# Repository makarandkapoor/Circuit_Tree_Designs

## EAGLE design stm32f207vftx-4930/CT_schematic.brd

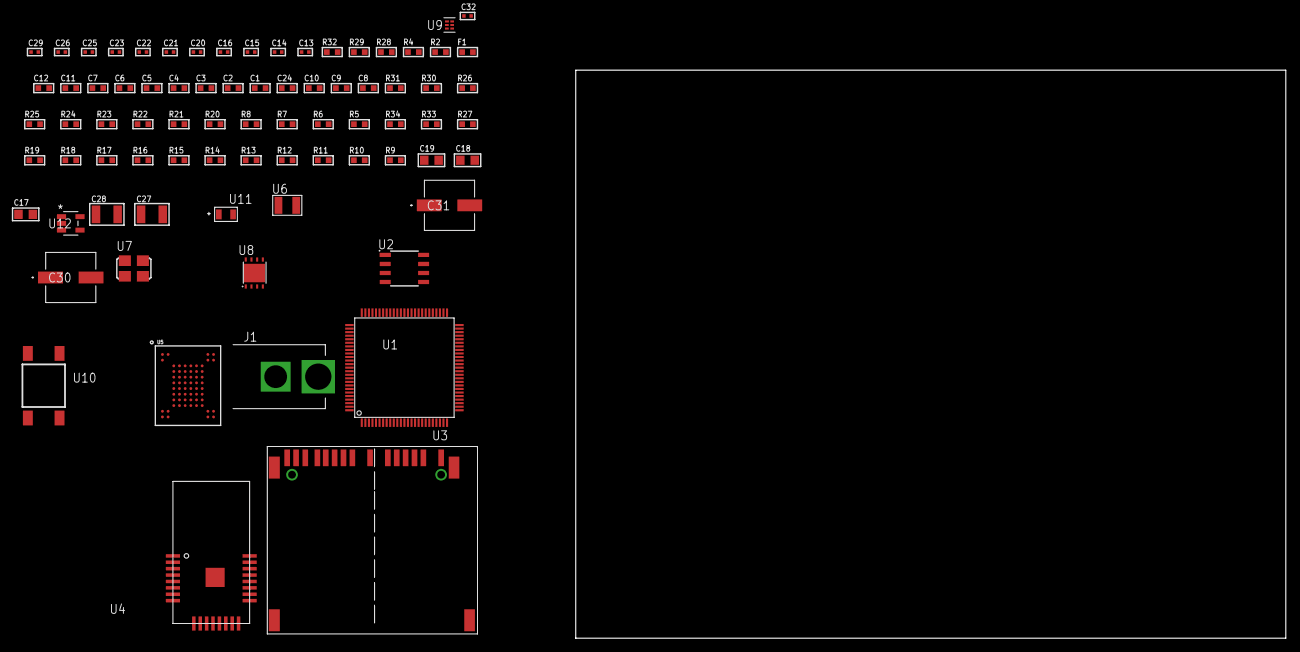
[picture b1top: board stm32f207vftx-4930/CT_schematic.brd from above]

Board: 2 copper layers, 100.0 x 80.0 mm, 78 parts (0 on the bottom side), 53 nets, no tracks yet.

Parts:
C1, C12: 1e-06; C0603
C2, C3, C4, C5, C6, C7: 1e-07; C0603
C8: 4.7e-06; C0603
C9, C10, C24: 2.2e-06; C0603
C11: 1e-08; C0603
C13, C14: 1e-11; C0402
C15, C25, C26, C32: 1e-08; C0402
C16, C20, C21, C22, C23, C29: 1e-07; C0402
C17, C18, C19: 1e-05; C0805
C27, C28: 1e-05; C1210
C30, C31: 0.0001; EXV-9H
F1: 240.0; L0603
J1: PJ-037B; PJ-037B_PACKAGE
R2, R29: 1000.0; R0603
R4: 4700.0; R0603
R5, R6, R7, R8, R20, R21, R22, R23, R24, R25, R26, R30, R31: 10000.0; R0603
R9, R10, R11, R12, R13, R14, R15, R16, R17, R18, R19, R27: 100000.0; R0603
R28: 2231.0; R0603
R32: 9100.0; R0603
R33: 680000.0; R0603
R34: 120000.0; R0603
U1: STM32F207VFT6; LQFP100
U2: AT25160B-SSHL-T; SOIC-8
U3: 10100565
U4: ATBTLC1000-MR110CA
U5: mt29f4g08abadah4; VFBGA-63
U6: ABS07-32.768KHZ-7-T
U7: ASFL1-25MHZ-NCS; ASFL1
U8: LP3878SDX-ADJ/NOPB; WSON-8
U9: TPS3895ADRYR; SON-6
U10: 4-1437565-2; SW_4-1437565-2
U11: Q65110A2395; LGM67K-G1J2-24-Z
U12: nc7sz125m5x; NC7SZ125M5X

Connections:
CLK_CRYSTAL_U1_8: C13.1, U1.8, U6.1
CLK_CRYSTAL_U1_9: C14.1, U1.9, U6.2
CLK_U1_12: U1.12, U7.3
GND: C1.2, C2.2, C3.2, C4.2, C5.2, C6.2, C7.2, C8.2, C9.2, C10.2, C11.2, C12.2, C13.2, C14.2, C15.2, C16.2, C17.2, C18.2, C19.2, C20.2, C21.2, C22.2, C23.2, C24.2, C25.2, C26.2, C27.2, C28.2, C29.2, C30.2, C31.2, C32.2, J1.2, R2.2, R5.2, R29.2, R32.2, R34.2, U1.10, U1.20, U1.27, U1.74, U2.4, U3.6, U3.10, U3.12, U3.16, U3.17, U3.20, U3.21, U4.1, U4.9, U4.13, U4.24, U4.25, U5.C5, U5.F7, U5.K3, U5.K8, U7.2, U8.3, U8.PAD, U9.2, U11.C, U12.1, U12.3
NET_U1_14: R4.1, U1.14, U12.4
NET_U1_22: C11.1, C12.1, F1.1, U1.21, U1.22
NET_U1_49: C9.1, U1.49
NET_U1_73: C10.1, U1.73
NET_U1_94: R5.1, U1.94
NET_U1_98: U10.3, U10.4
NET_U2_3: R6.1, U2.3
NET_U2_7: R8.1, U2.7
NET_U3_1: R11.1, U3.1
NET_U3_2: R10.1, U3.2
NET_U3_18: U3.18, U3.19
NET_U4_17: R20.1, U4.17
NET_U4_20: R21.1, U4.20
NET_U5_C3: R26.1, U5.C3
NET_U8_1: C26.1, U8.1
NET_U8_6: R28.2, R29.1, U8.6
NET_U8_8: R27.1, U8.8
NET_U9_1: R31.1, R32.1, U9.1
NET_U9_3: R33.2, R34.1, U9.3
NET_U9_4: R30.1, U9.4, U12.2
NET_U10_1: R2.1, U10.1, U10.2
PROC_FSMC_D0: U1.61, U5.H4
PROC_FSMC_D1: U1.62, U5.J4
PROC_FSMC_D2: U1.81, U5.K4
PROC_FSMC_D3: U1.82, U5.K5
PROC_FSMC_D4: U1.38, U5.K6
PROC_FSMC_D5: U1.39, U5.J7
PROC_FSMC_D6: U1.40, U5.K7
PROC_FSMC_D7: U1.41, U5.J8
PROC_FSMC_NCE2: R23.1, U1.88, U5.C6
PROC_FSMC_NOE: R25.1, U1.85, U5.D4
PROC_FSMC_NWAIT: R22.1, U1.87, U5.C8
PROC_FSMC_NWE: R24.1, U1.86, U5.C7
PROC_SDIO_CK: R9.1, U1.80, U3.8
PROC_SDIO_D0: R12.1, U1.65, U3.4
PROC_SDIO_D1: R13.1, U1.66, U3.3
PROC_SDIO_D2: R14.1, U1.78, U3.15
PROC_SDIO_D3: R15.1, U1.79, U3.14
PROC_SDIO_D4: R16.1, U1.95, U3.13
PROC_SDIO_D5: R17.1, U1.96, U3.11
PROC_SDIO_D6: R18.1, U1.63, U3.7
PROC_SDIO_D7: R19.1, U1.64, U3.5
PROC_SPI1_MISO: U1.31, U4.14
PROC_SPI1_MOSI: U1.32, U4.11
PROC_SPI1_NSS: U1.29, U4.12
PROC_SPI1_SCK: U1.30, U4.10
PROC_SPI2_NSS: R7.1, U2.1
VCC_S1_15V8: C27.1, C30.1, C31.1, J1.1, R27.2, U8.4
VCC_TIER1_3V3: C1.1, C2.1, C3.1, C4.1, C5.1, C6.1, C7.1, C8.1, C15.1, C16.1, C17.1, C18.1, C19.1, C20.1, C21.1, C22.1, C23.1, C24.1, C25.1, C28.1, C29.1, C32.1, F1.2, R4.2, R6.2, R7.2, R8.2, R9.2, R10.2, R11.2, R12.2, R13.2, R14.2, R15.2, R16.2, R17.2, R18.2, R19.2, R20.2, R21.2, R22.2, R23.2, R24.2, R25.2, R26.2, R28.1, R30.2, R31.2, R33.1, U1.6, U1.11, U1.19, U1.28, U1.50, U1.75, U1.100, U2.8, U3.9, U4.6, U4.22, U5.D3, U5.G4, U5.H8, U5.J6, U7.4, U8.5, U9.6, U12.5

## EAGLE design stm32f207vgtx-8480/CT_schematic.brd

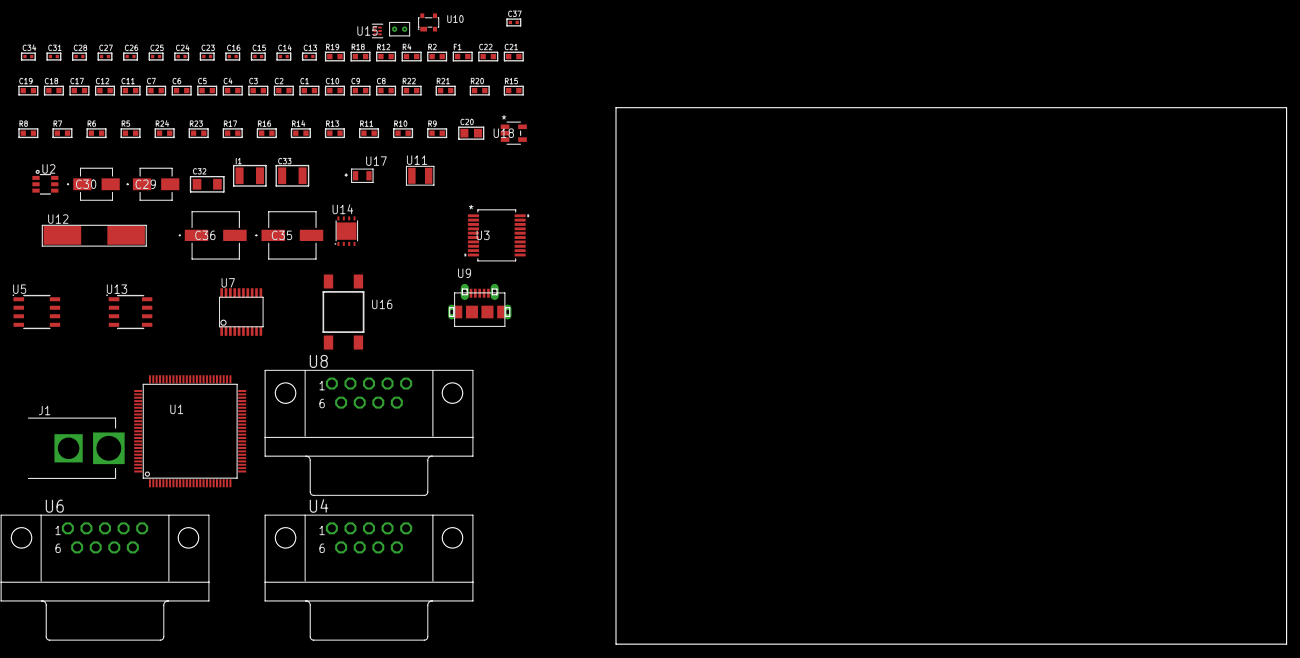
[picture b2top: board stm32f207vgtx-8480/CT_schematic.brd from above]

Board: 2 copper layers, 124.8 x 80.0 mm, 81 parts (0 on the bottom side), 63 nets, no tracks yet.

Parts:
C1, C12, C17, C18, C19, C21, C22: 1e-06; C0603
C2, C3, C4, C5, C6, C7: 1e-07; C0603
C8: 4.7e-06; C0603
C9, C10: 2.2e-06; C0603
C11: 1e-08; C0603
C13, C14, C15, C16: 1e-11; C0402
C20: 4.7e-06; C0805
C23, C24, C25, C26, C27, C28, C34: 1e-07; C0402
C29: 1e-06; EXV-9B
C30: 2.2e-06; EXV-9B
C31, C37: 1e-08; C0402
C32: 1e-05; C1206
C33: 1e-05; C1210
C35, C36: 0.0001; EXV-9H
F1: 240.0; L0603
I1: 1.5e-05; L1210
J1: PJ-037B; PJ-037B_PACKAGE
R2, R19: 1000.0; R0603
R4: 4700.0; R0603
R5, R15: 47000.0; R0603
R6, R7, R8, R20, R21: 10000.0; R0603
R9, R10, R11, R13, R14, R16, R17: 100000.0; R0603
R12: 120.0; R0603
R18: 3900.0; R0603
R22: 82000.0; R0603
R23: 300000.0; R0603
R24: 120000.0; R0603
U1: STM32f207VGT6; LQFP100
U2: MAX4995AAUT+T; SOT-23-6
U3: MAX3218EAP+T; SSOP-20
U4, U6, U8: 182-009-113R531; 182-009-MALE
U5: MCP2562-E/SN; SOIC-8
U7: SP3203ECY-L/TR; TSSOP20-I
U9: 47590-0001; MICRO_USB_AB
U10: prtr5v0u2ax; SOT143B
U11: ABS07-32.768KHZ-7-T
U12: ABLS-25.000MHZ-B2F-T
U13: LP2954AIMX/NOPB; LP2954
U14: LP3878SDX-ADJ/NOPB; WSON-8
U15: TPS3895ADRYR; SON-6
U16: 4-1437565-2; SW_4-1437565-2
U17: Q65110A2395; LGM67K-G1J2-24-Z
U18: nc7sz125m5x; NC7SZ125M5X
U19: Dummy; DUMMY_PACKAGE_173

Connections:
CLK_CRYSTAL_U1_8: C13.1, U1.8, U11.1
CLK_CRYSTAL_U1_9: C14.1, U1.9, U11.2
CLK_CRYSTAL_U1_12: C15.1, U1.12, U12.1
CLK_CRYSTAL_U1_13: C16.1, U1.13, U12.2
GND: C1.2, C2.2, C3.2, C4.2, C5.2, C6.2, C7.2, C8.2, C9.2, C10.2, C11.2, C12.2, C13.2, C14.2, C15.2, C16.2, C17.2, C18.2, C19.2, C21.2, C22.2, C23.2, C24.2, C27.2, C28.2, C29.2, C30.2, C31.2, C32.2, C33.2, C34.2, C35.2, C36.2, C37.2, J1.2, R2.2, R5.2, R6.2, R8.2, R16.2, R19.2, R22.2, R24.2, U1.10, U1.20, U1.27, U1.74, U2.2, U3.5, U3.17, U3.20, U4.5, U5.2, U5.8, U6.5, U7.18, U8.5, U9.5, U9.6, U9.7, U9.8, U9.9, U10.1, U13.4, U14.3, U14.PAD, U15.2, U17.C, U18.1, U18.3, U19.1
NET_U1_14: R4.1, U1.14, U18.4
NET_U1_22: C11.1, C12.1, F1.1, U1.21, U1.22
NET_U1_49: C9.1, U1.49
NET_U1_73: C10.1, U1.73
NET_U1_94: R6.1, U1.94
NET_U1_98: U16.3, U16.4
NET_U2_3: R5.1, U2.3
NET_U3_1: I1.1, U3.1
NET_U3_2: R9.1, U3.2
NET_U3_3: R10.1, U3.3
NET_U3_4: R11.1, U3.4
NET_U3_15: C19.1, U3.15
NET_U3_16: C20.2, U3.16
NET_U3_18: C20.1, U3.18
NET_U3_19: C18.1, U3.19
NET_U4_2: U3.12, U4.2
NET_U4_3: U3.14, U4.3
NET_U4_7: U3.11, U4.7
NET_U4_8: U3.13, U4.8
NET_U5_6: R12.2, U5.6
NET_U6_2: R12.2, U5.6, U6.2
NET_U6_3: R12.1, U5.7, U6.3
NET_U7_1: C25.1, U7.1
NET_U7_2: C27.1, U7.2
NET_U7_3: C25.2, U7.3
NET_U7_4: C26.1, U7.4
NET_U7_5: C26.2, U7.5
NET_U7_6: C28.1, U7.6
NET_U8_2: U7.14, U8.2
NET_U8_3: U7.17, U8.3
NET_U8_7: U7.13, U8.7
NET_U8_8: U7.16, U8.8
NET_U13_3: R14.1, U13.3
NET_U13_5: R13.1, U13.5
NET_U13_7: R15.2, R16.1, U13.7
NET_U14_1: C31.1, U14.1
NET_U14_6: R18.2, R19.1, U14.6
NET_U14_8: R17.1, U14.8
NET_U15_1: R21.1, R22.1, U15.1
NET_U15_3: R23.2, R24.1, U15.3
NET_U15_4: R20.1, U15.4, U18.2
NET_U16_1: R2.1, U16.1, U16.2
PROC_CAN1_RX: U1.81, U5.4
PROC_CAN1_TX: U1.82, U5.1
PROC_DAC_OUT2: U1.30, U19.2
PROC_GPIO_TO_U1_USB_FAULT: R7.1, U1.2, U2.6
PROC_GPIO_TO_U1_VBUS_EN: R8.1, U1.1, U2.4
PROC_UART4_RX: U1.24, U7.11
PROC_UART4_TX: U1.23, U7.7
PROC_UART5_RX: U1.83, U3.9
PROC_UART5_TX: U1.80, U3.7
PROC_USB_OTG_FS_DM: U1.70, U9.2, U10.3
PROC_USB_OTG_FS_DP: U1.71, U9.3, U10.2
PROC_USB_OTG_FS_ID: U1.69, U9.4
PROC_USB_OTG_FS_VBUS: U1.68, U2.1, U9.1, U10.4
VCC_S1_9V3: C29.1, C32.1, C35.1, C36.1, J1.1, R14.2, R17.2, U13.8, U14.4
VCC_TIER1_1V8: C1.1, C2.1, C3.1, C4.1, C5.1, C6.1, C7.1, C8.1, C17.1, C22.1, C24.1, C30.1, C34.1, C37.1, F1.2, I1.2, R4.2, R7.2, R9.2, R10.2, R11.2, R13.2, R15.1, R20.2, R21.2, R23.1, U1.6, U1.11, U1.19, U1.28, U1.50, U1.75, U1.100, U3.6, U5.5, U7.12, U13.1, U15.6, U18.5
VCC_TIER1_5V0: C21.1, C23.1, C33.1, R18.1, U2.5, U5.3, U7.19, U14.5

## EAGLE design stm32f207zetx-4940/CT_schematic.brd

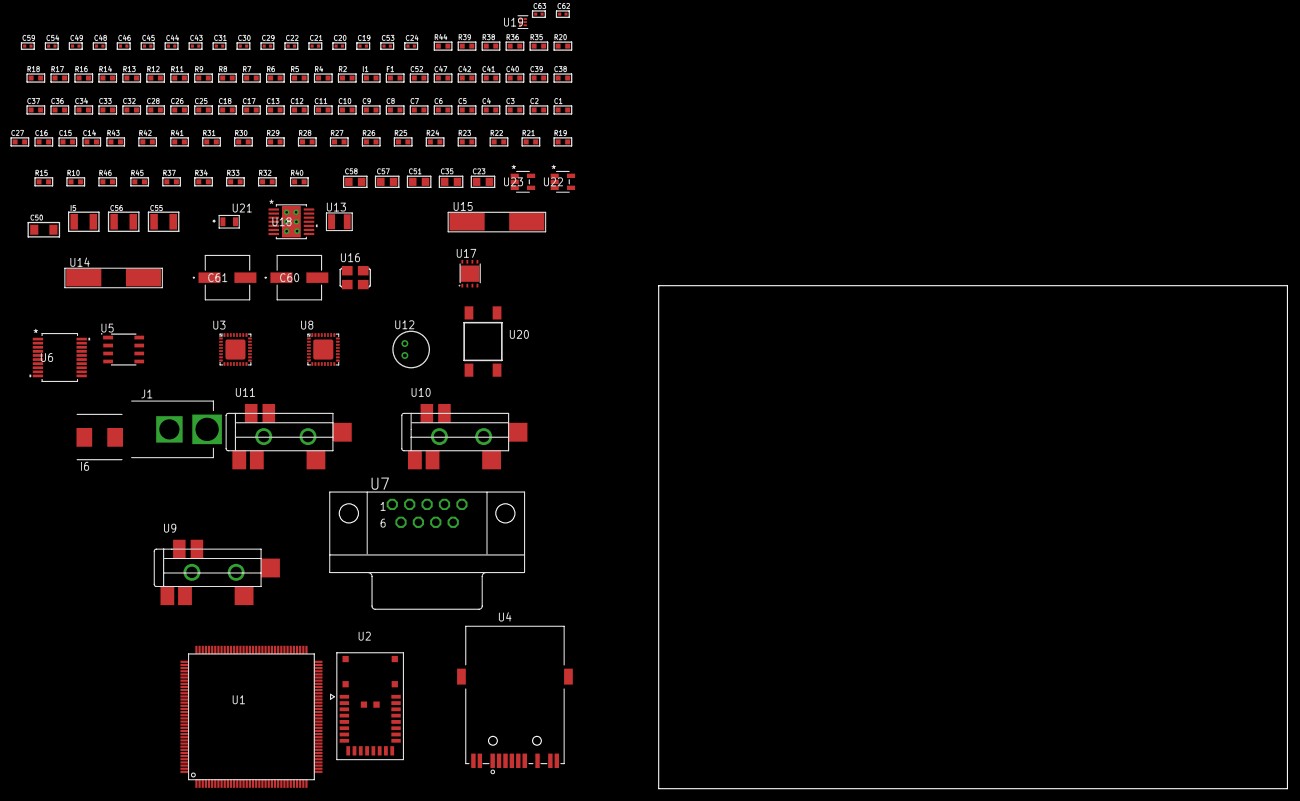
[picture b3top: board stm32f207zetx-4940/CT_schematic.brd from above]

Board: 2 copper layers, 100.0 x 80.0 mm, 135 parts (0 on the bottom side), 101 nets, no tracks yet.

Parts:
C1, C18, C25, C26, C28, C32, C33, C34, C36, C37, C38, C39, C40, C41, C42, C47, C52: 1e-06; C0603
C2, C3, C4, C5, C6, C7, C8, C9, C10, C11, C12, C13: 1e-07; C0603
C14: 4.7e-06; C0603
C15, C16: 2.2e-06; C0603
C17: 1e-08; C0603
C19, C20, C21, C22, C29, C30: 1e-11; C0402
C23, C51, C57, C58: 1e-05; C0805
C24: 2.2e-08; C0402
C27: 4.7e-10; C0603
C31, C48, C49, C62, C63: 1e-08; C0402
C35: 4.7e-06; C0805
C43, C44, C45, C46, C54, C59: 1e-07; C0402
C50: 1e-05; C1206
C53: 3.3e-09; C0402
C55, C56: 2.2e-05; C1210
C60, C61: 0.0001; EXV-9H
F1: 240.0; L0603
I1: 97.0; R0603
I5: 1.5e-05; L1210
I6: 3.3e-06; WE-HCI_7030/7040/7050
J1: PJ-037B; PJ-037B_PACKAGE
R2, R39: 1000.0; R0603
R4, R5: 4700.0; R0603
R6, R7, R8, R9: 2200.0; R0603
R10, R19, R21, R22, R23, R24, R25, R26, R27, R28, R29, R30, R31, R42, R43: 10000.0; R0603
R11, R12: 0.1; R0603
R13, R14, R38: 200.0; R0603
R15: 12100.0; R0603
R16, R17, R18, R20: 49.9; R0603
R32, R33, R34, R37: 100000.0; R0603
R35, R36: 1270.0; R0603
R40: 71007.101651032; R0603
R41: 22000.0; R0603
R44: 9100.0; R0603
R45: 680000.0; R0603
R46: 120000.0; R0603
U1: STM32F207ZET6; LQFP144
U2: A2500R24A00GM
U3: LAN8710AI-EZK; QFN-32
U4: 7498011122R
U5: AT24C02D-SSHM-T; AT24C02D
U6: MAX3218EAP+T; SSOP-20
U7: 182-009-113R531; 182-009-MALE
U8: SGTL5000XNAA3; QFN-32
U9, U10, U11: SJ-43515TS-SMT-TR
U12: WM-64PCT; WM-64PC
U13: ABS07-32.768KHZ-7-T
U14, U15: ABLS-25.000MHZ-B2F-T
U16: ASFL-24.57MHZ-NCS; ASFL1
U17: LP3878SDX-ADJ/NOPB; WSON-8
U18: tps54325PWP; HTSSOP14
U19: TPS3895ADRYR; SON-6
U20: 4-1437565-2; SW_4-1437565-2
U21: Q65110A2395; LGM67K-G1J2-24-Z
U22, U23: nc7sz125m5x; NC7SZ125M5X

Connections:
CLK_CRYSTAL_U1_8: C19.1, U1.8, U13.1
CLK_CRYSTAL_U1_9: C20.1, U1.9, U13.2
CLK_CRYSTAL_U1_23: C21.1, U1.23, U14.1
CLK_CRYSTAL_U1_24: C22.1, U1.24, U14.2
CLK_CRYSTAL_U3_4: C30.1, U3.4, U15.2
CLK_CRYSTAL_U3_5: C29.1, U3.5, U15.1
CLK_U8_21: U8.21, U16.3
GND: C1.2, C2.2, C3.2, C4.2, C5.2, C6.2, C7.2, C8.2, C9.2, C10.2, C11.2, C12.2, C13.2, C14.2, C15.2, C16.2, C17.2, C18.2, C19.2, C20.2, C21.2, C22.2, C23.2, C24.2, C25.2, C26.2, C27.2, C28.2, C29.2, C30.2, C31.2, C32.2, C33.2, C34.2, C43.2, C44.2, C45.2, C46.2, C47.2, C48.2, C49.2, C50.2, C51.2, C52.2, C53.2, C55.2, C56.2, C57.2, C58.2, C59.2, C60.2, C61.2, C62.2, C63.2, J1.2, R2.2, R10.2, R11.2, R12.2, R13.2, R15.2, R26.2, R27.2, R28.2, R30.2, R31.2, R36.2, R39.2, R41.2, R44.2, R46.2, U1.16, U1.31, U1.38, U1.51, U1.61, U1.83, U1.94, U1.107, U1.120, U1.130, U2.8, U2.17, U3.EXP, U5.4, U6.5, U6.17, U6.20, U7.5, U8.1, U8.3, U8.7, U8.EXP, U10.1, U11.1, U12.2, U16.2, U17.3, U17.PAD, U18.5, U18.8, U18.9, U18.15, U19.2, U21.C, U22.1, U22.3, U23.1, U23.3
NET_U1_25: R5.1, U1.25, U23.4
NET_U1_27: R8.1, U1.27, U3.17
NET_U1_33: C17.1, C18.1, F1.1, U1.32, U1.33
NET_U1_36: R9.1, U1.36, U3.16
NET_U1_71: C15.1, U1.71
NET_U1_106: C16.1, U1.106
NET_U1_136: R6.1, U1.136, U5.6
NET_U1_137: R7.1, U1.137, U5.5
NET_U1_138: R10.1, U1.138
NET_U1_142: U20.3, U20.4
NET_U3_1: C25.1, I1.1, R16.2, R17.2, R18.2, R20.2, R21.2, U3.1, U3.27, U4.2, U4.9
NET_U3_3: R21.1, U3.3
NET_U3_18: R19.1, U3.18
NET_U3_19: R4.1, U3.19, U22.4
NET_U3_32: R15.1, U3.32
NET_U4_1: R16.1, U3.29, U4.1
NET_U4_3: R14.2, R17.1, U3.28, U4.3
NET_U4_4: R18.1, U3.31, U4.4
NET_U4_5: C24.1, U4.2, U4.5
NET_U4_6: R20.1, U3.30, U4.6
NET_U4_8: R12.1, U4.8
NET_U4_10: R14.1, U4.10
NET_U4_11: U3.2, U4.11
NET_U4_12: R13.1, U4.12
NET_U4_13: R11.1, U4.13, U4.14
NET_U5_1: R29.1, U5.1
NET_U5_2: R30.1, U5.2
NET_U5_3: R31.1, U5.3
NET_U5_7: R28.1, U5.7
NET_U6_1: I5.1, U6.1
NET_U6_2: R32.1, U6.2
NET_U6_3: R33.1, U6.3
NET_U6_4: R34.1, U6.4
NET_U6_15: C34.1, U6.15
NET_U6_16: C35.2, U6.16
NET_U6_18: C35.1, U6.18
NET_U6_19: C33.1, U6.19
NET_U7_2: U6.12, U7.2
NET_U7_3: U6.14, U7.3
NET_U7_7: U6.11, U7.7
NET_U7_8: U6.13, U7.8
NET_U8_10: C46.1, U8.10
NET_U8_29: R35.1, U8.29
NET_U8_31: R36.1, U8.31
NET_U9_1: U8.4, U9.1
NET_U9_2: U8.2, U9.2
NET_U9_5: U8.6, U9.5
NET_U10_2: C37.1, U10.2
NET_U10_5: C36.1, U10.5
NET_U11_2: C39.1, C40.1, U11.2
NET_U11_5: C38.1, U11.5
NET_U11_13: C39.2, C40.2
NET_U12_1: C41.1, C42.1, C47.1, U8.16, U12.1
NET_U12_15: C41.2, C42.2
NET_U17_1: C49.1, U17.1
NET_U17_6: R38.2, R39.1, U17.6
NET_U17_8: R37.1, U17.8
NET_U18_2: R40.2, R41.1, U18.2
NET_U18_3: C52.1, U18.3
NET_U18_4: C53.1, U18.4
NET_U18_10: C54.1, I6.1, U18.10, U18.11
NET_U18_12: C54.2, U18.12
NET_U19_1: R43.1, R44.1, U19.1
NET_U19_3: R45.2, R46.1, U19.3
NET_U19_4: R42.1, U19.4, U22.2, U23.2
NET_U20_1: R2.1, U20.1, U20.2
PROC_ETH_COL: R24.1, U1.37, U3.15
PROC_ETH_CRS: U1.34, U3.14
PROC_ETH_RXD0: R22.1, U1.44, U3.11
PROC_ETH_RXD1: R23.1, U1.45, U3.10
PROC_ETH_RXD2: U1.46, U3.9
PROC_ETH_RXD3: R27.1, U1.47, U3.8
PROC_ETH_RX_CLK: R26.1, U1.35, U3.7
PROC_ETH_RX_DV: U1.43, U3.26
PROC_ETH_RX_ER: R25.1, U1.69, U3.13
PROC_ETH_TXD0: U1.73, U3.22
PROC_ETH_TXD1: U1.129, U3.23
PROC_ETH_TXD2: U1.28, U3.24
PROC_ETH_TXD3: U1.1, U3.25
PROC_ETH_TX_CLK: U1.29, U3.20
PROC_ETH_TX_EN: U1.70, U3.21
PROC_I2S2_SCK: U1.74, U8.24
PROC_I2S2_SD: U1.76, U8.26
PROC_I2S2_WS: U1.140, U8.23
PROC_SPI1_MISO: U1.42, U2.10
PROC_SPI1_MOSI: U1.135, U2.11
PROC_SPI1_NSS: U1.40, U2.12
PROC_SPI1_SCK: U1.41, U2.9
PROC_UART4_RX: U1.112, U6.9
PROC_UART4_TX: U1.111, U6.7
VCC_S1_6V1: C50.1, C57.1, C58.1, C60.1, C61.1, J1.1, R37.2, U17.4, U18.7, U18.13, U18.14
VCC_TIER1_1V2: C26.1, C27.1, C43.1, C51.1, R38.1, U3.6, U8.30, U17.5
VCC_TIER1_3V3: C1.1, C2.1, C3.1, C4.1, C5.1, C6.1, C7.1, C8.1, C9.1, C10.1, C11.1, C12.1, C13.1, C14.1, C23.1, C28.1, C31.1, C32.1, C44.1, C45.1, C48.1, C55.1, C56.1, C59.1, C62.1, C63.1, F1.2, I1.2, I5.2, I6.2, R4.2, R5.2, R6.2, R7.2, R8.2, R9.2, R19.2, R22.2, R23.2, R24.2, R25.2, R29.2, R32.2, R33.2, R34.2, R35.2, R40.1, R42.2, R43.2, R45.1, U1.6, U1.17, U1.30, U1.39, U1.52, U1.62, U1.72, U1.84, U1.95, U1.108, U1.121, U1.131, U1.144, U2.18, U3.12, U5.8, U6.6, U8.5, U8.20, U16.4, U18.1, U19.6, U22.5, U23.5

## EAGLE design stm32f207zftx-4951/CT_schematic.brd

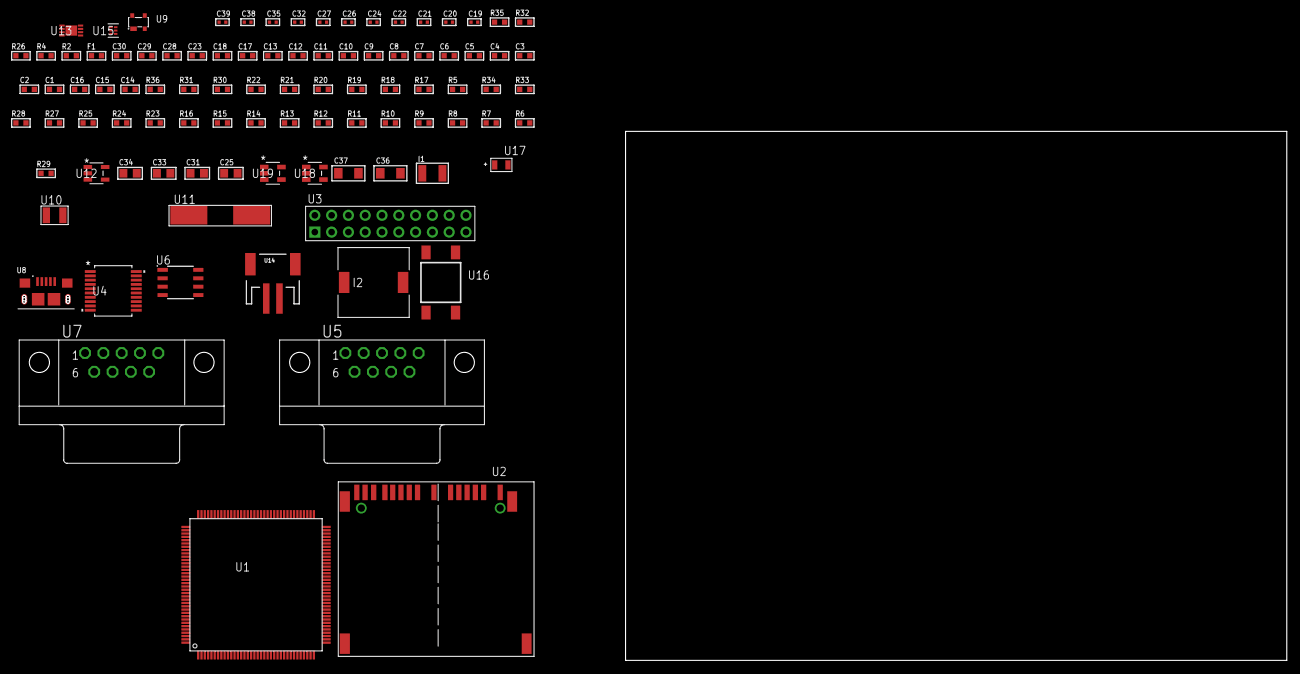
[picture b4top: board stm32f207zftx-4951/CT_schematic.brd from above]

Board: 2 copper layers, 95 parts (0 on the bottom side), 64 nets, no tracks yet.

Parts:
C1, C18, C23, C28, C29, C30: 1e-06; C0603
C2, C3, C4, C5, C6, C7, C8, C9, C10, C11, C12, C13: 1e-07; C0603
C14: 4.7e-06; C0603
C15, C16: 2.2e-06; C0603
C17: 1e-08; C0603
C19, C20, C21, C22: 1e-11; C0402
C24, C26, C27, C32, C35: 1e-07; C0402
C25, C33, C34: 1e-05; C0805
C31: 4.7e-06; C0805
C36, C37: 1e-05; C1206
C38, C39: 1e-08; C0402
F1: 240.0; L0603
I1: 1.5e-05; L1210
I2: 2.5e-06; DR1040
R2: 1000.0; R0603
R4: 4700.0; R0603
R5, R17, R18, R19, R20, R21, R22, R30, R31, R36: 10000.0; R0603
R6, R7, R8, R9, R10, R11, R12, R13, R14, R15, R16, R23, R24, R25: 100000.0; R0603
R26: 120.0; R0603
R27: 470000.0; R0603
R28: 220000.0; R0603
R29: 1000000.0; R0603
R32: 9100.0; R0603
R33: 680000.0; R0603
R34: 120000.0; R0603
R35: 2000.0; R0603
U1: STM32F207ZFT6; LQFP144
U2: 10100565
U3: TST-110-05-T-D-RA
U4: MAX3218EAP+T; SSOP-20
U5, U7: 182-009-113R531; 182-009-MALE
U6: SN65HVD230D; SOIC-8
U8: 10118193-0001LF; FCI_10118193-0001LF
U9: prtr5v0u2ax; SOT143B
U10: ABS07-32.768KHZ-7-T
U11: ABLS-25.000MHZ-B2F-T
U12: ltc3406es5; TSOT-23-5
U13: MCP73831T-2ACI/MC; DFN8_2X3MC
U14: S2B-PH-SM4-TB(LF)(SN); JST-2-SMD
U15: TPS3895ADRYR; SON-6
U16: 4-1437565-2; SW_4-1437565-2
U17: Q65110A2395; LGM67K-G1J2-24-Z
U18, U19: nc7sz125m5x; NC7SZ125M5X

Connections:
CLK_CRYSTAL_U1_8: C19.1, U1.8, U10.1
CLK_CRYSTAL_U1_9: C20.1, U1.9, U10.2
CLK_CRYSTAL_U1_23: C21.1, U1.23, U11.1
CLK_CRYSTAL_U1_24: C22.1, U1.24, U11.2
GND: C1.2, C2.2, C3.2, C4.2, C5.2, C6.2, C7.2, C8.2, C9.2, C10.2, C11.2, C12.2, C13.2, C14.2, C15.2, C16.2, C17.2, C18.2, C19.2, C20.2, C21.2, C22.2, C23.2, C24.2, C25.2, C26.2, C27.2, C28.2, C29.2, C30.2, C32.2, C33.2, C34.1, C34.2, C35.2, C36.2, C37.2, C38.2, C39.2, R2.2, R5.2, R22.2, R27.2, R28.2, R32.2, R34.2, R35.2, U1.16, U1.31, U1.38, U1.51, U1.61, U1.83, U1.94, U1.103, U1.107, U1.120, U1.130, U2.6, U2.10, U2.12, U2.16, U2.17, U2.20, U2.21, U3.4, U3.6, U3.8, U3.10, U3.12, U3.14, U3.16, U3.18, U3.20, U4.5, U4.17, U4.20, U5.5, U6.2, U7.5, U8.5, U8.6, U8.7, U8.8, U8.9, U9.1, U12.2, U13.6, U13.9, U14.2, U15.2, U17.C, U18.2, U18.3, U19.1, U19.3
INPUT_USBPOWER_5V: C23.1, C36.1, R36.2, U1.101, U8.1, U9.4, U13.1, U13.2
NET_U1_25: R4.1, U1.25, U19.4
NET_U1_33: C17.1, C18.1, F1.1, U1.32, U1.33
NET_U1_71: C15.1, U1.71
NET_U1_106: C16.1, U1.106
NET_U1_138: R5.1, U1.138
NET_U1_142: U16.3, U16.4
NET_U2_1: R8.1, U2.1
NET_U2_2: R7.1, U2.2
NET_U2_18: U2.18, U2.19
NET_U3_19: R22.1, U3.19
NET_U4_1: I1.1, U4.1
NET_U4_2: R23.1, U4.2
NET_U4_3: R24.1, U4.3
NET_U4_4: R25.1, U4.4
NET_U4_15: C30.1, U4.15
NET_U4_16: C31.2, U4.16
NET_U4_18: C31.1, U4.18
NET_U4_19: C29.1, U4.19
NET_U5_2: U4.12, U5.2
NET_U5_3: U4.14, U5.3
NET_U5_7: U4.11, U5.7
NET_U5_8: U4.13, U5.8
NET_U6_6: R26.2, U6.6
NET_U6_8: R27.1, U6.8
NET_U7_2: R26.2, U6.6, U7.2
NET_U7_3: R26.1, U6.7, U7.3
NET_U12_3: I2.1, U12.3
NET_U12_5: R28.1, R29.1, U12.5
NET_U12_ATNET_3: I2.2, R29.2
NET_U13_5: R36.1, U13.5
NET_U13_8: R35.1, U13.8
NET_U15_1: R31.1, R32.1, U15.1
NET_U15_3: R33.2, R34.1, U15.3
NET_U15_4: R30.1, U15.4, U18.4, U19.2
NET_U16_1: R2.1, U16.1, U16.2
PROC_CAN1_RX: U1.114, U6.4
PROC_CAN1_TX: U1.115, U6.1
PROC_SDIO_CK: R6.1, U1.113, U2.8
PROC_SDIO_D0: R9.1, U1.98, U2.4
PROC_SDIO_D1: R10.1, U1.99, U2.3
PROC_SDIO_D2: R11.1, U1.111, U2.15
PROC_SDIO_D3: R12.1, U1.112, U2.14
PROC_SDIO_D4: R13.1, U1.139, U2.13
PROC_SDIO_D5: R14.1, U1.140, U2.11
PROC_SDIO_D6: R15.1, U1.96, U2.7
PROC_SDIO_D7: R16.1, U1.97, U2.5
PROC_SYS_JTDI: R18.1, U1.110, U3.5
PROC_SYS_JTDO_SWO: U1.133, U3.13
PROC_SYS_JTMS_SWDIO: R19.1, U1.105, U3.7
PROC_SYS_JTRST: R17.1, U1.134, U3.3
PROC_SYS_TRACECLK: R20.1, U1.1, U3.9
PROC_UART4_RX: U1.35, U4.9
PROC_UART4_TX: U1.34, U4.7
PROC_USB_OTG_FS_DM: U1.103, U8.2, U9.3
PROC_USB_OTG_FS_DP: U1.104, U8.3, U9.2
RST_OUT_U3_SRESET_B: R21.1, U3.15, U18.1
VCC_S1_3V7: C33.1, C37.1, U12.4, U13.3, U13.4, U14.1
VCC_TIER1_3V3: C1.1, C2.1, C3.1, C4.1, C5.1, C6.1, C7.1, C8.1, C9.1, C10.1, C11.1, C12.1, C13.1, C14.1, C24.1, C25.1, C26.1, C27.1, C28.1, C32.1, C34.2, C35.1, C38.1, C39.1, F1.2, I1.2, I2.2, R4.2, R6.2, R7.2, R8.2, R9.2, R10.2, R11.2, R12.2, R13.2, R14.2, R15.2, R16.2, R17.2, R18.2, R19.2, R20.2, R21.2, R23.2, R24.2, R25.2, R29.2, R30.2, R31.2, R33.1, U1.6, U1.17, U1.30, U1.39, U1.52, U1.62, U1.72, U1.84, U1.95, U1.108, U1.121, U1.131, U1.144, U2.9, U3.1, U3.2, U4.6, U6.3, U15.6, U18.5, U19.5

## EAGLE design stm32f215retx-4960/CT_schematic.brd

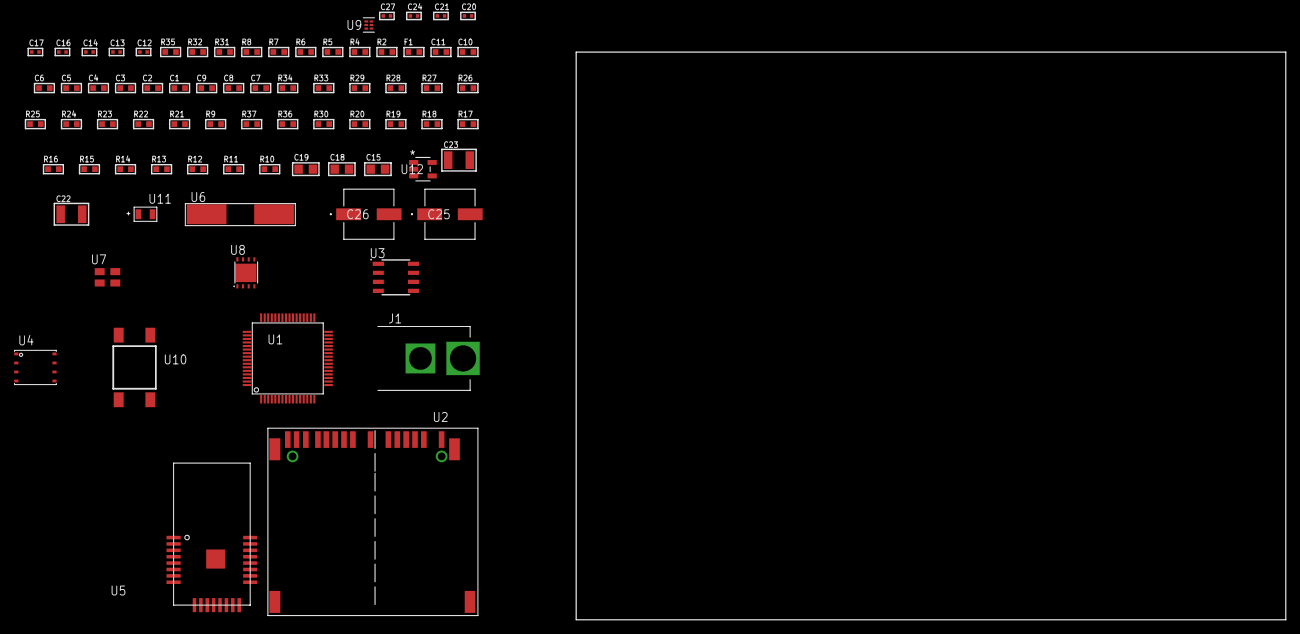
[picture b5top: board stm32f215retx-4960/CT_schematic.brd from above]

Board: 2 copper layers, 100.0 x 80.0 mm, 76 parts (0 on the bottom side), 48 nets, no tracks yet.

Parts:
C1, C11: 1e-06; C0603
C2, C3, C4, C5, C6: 1e-07; C0603
C7: 4.7e-06; C0603
C8, C9: 2.2e-06; C0603
C10: 1e-08; C0603
C12, C13: 1e-11; C0402
C14, C24: 1e-07; C0402
C15, C18, C19: 1e-05; C0805
C16, C17, C20, C21, C27: 1e-08; C0402
C22, C23: 1e-05; C1210
C25, C26: 0.0001; EXV-9H
F1: 240.0; L0603
J1: PJ-037B; PJ-037B_PACKAGE
R2, R32: 1000.0; R0603
R4: 4700.0; R0603
R5, R6, R7, R8: 2200.0; R0603
R9, R21, R22, R23, R24, R25, R26, R27, R28, R29, R33, R34: 10000.0; R0603
R10, R11, R12, R13, R14, R15, R16, R17, R18, R19, R20, R30: 100000.0; R0603
R31: 2231.0; R0603
R35: 9100.0; R0603
R36: 680000.0; R0603
R37: 120000.0; R0603
U1: STM32F215RET6; LQFP64
U2: 10100565
U3: AT24C02D-SSHM-T; AT24C02D
U4: 24AA256-I/MF; DFN8-S
U5: ATBTLC1000-MR110CA
U6: ABLS-25.000MHZ-B2F-T
U7: ASEK-32.768KHz-ECST; ASEK
U8: LP3878SDX-ADJ/NOPB; WSON-8
U9: TPS3895ADRYR; SON-6
U10: 4-1437565-2; SW_4-1437565-2
U11: Q65110A2395; LGM67K-G1J2-24-Z
U12: nc7sz125m5x; NC7SZ125M5X

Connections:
CLK_CRYSTAL_U1_5: C12.1, U1.5, U6.1
CLK_CRYSTAL_U1_6: C13.1, U1.6, U6.2
CLK_U1_3: U1.3, U7.3
GND: C1.2, C2.2, C3.2, C4.2, C5.2, C6.2, C7.2, C8.2, C9.2, C10.2, C11.2, C12.2, C13.2, C14.2, C15.2, C16.2, C17.2, C18.2, C19.2, C20.2, C21.2, C22.2, C23.2, C24.2, C25.2, C26.2, C27.2, J1.2, R2.2, R9.2, R21.2, R23.2, R24.2, R25.2, R26.2, R32.2, R35.2, R37.2, U1.12, U1.18, U1.63, U2.6, U2.10, U2.12, U2.16, U2.17, U2.20, U2.21, U3.4, U4.4, U5.1, U5.9, U5.13, U5.24, U5.25, U7.2, U8.3, U8.PAD, U9.2, U11.C, U12.1, U12.3
NET_U1_7: R4.1, U1.7, U12.4
NET_U1_13: C10.1, C11.1, F1.1, U1.13
NET_U1_29: R7.1, U1.29, U3.6
NET_U1_30: R8.1, U1.30, U3.5
NET_U1_31: C8.1, U1.31
NET_U1_47: C9.1, U1.47
NET_U1_57: U10.3, U10.4
NET_U1_58: R5.1, U1.58, U4.6
NET_U1_59: R6.1, U1.59, U4.5
NET_U1_60: R9.1, U1.60
NET_U2_1: R12.1, U2.1
NET_U2_2: R11.1, U2.2
NET_U2_18: U2.18, U2.19
NET_U3_1: R22.1, U3.1
NET_U3_2: R23.1, U3.2
NET_U3_3: R24.1, U3.3
NET_U3_7: R21.1, U3.7
NET_U4_1: R25.1, U4.1
NET_U4_2: R26.1, U4.2
NET_U4_3: R27.1, U4.3
NET_U5_17: R28.1, U5.17
NET_U5_20: R29.1, U5.20
NET_U8_1: C21.1, U8.1
NET_U8_6: R31.2, R32.1, U8.6
NET_U8_8: R30.1, U8.8
NET_U9_1: R34.1, R35.1, U9.1
NET_U9_3: R36.2, R37.1, U9.3
NET_U9_4: R33.1, U9.4, U12.2
NET_U10_1: R2.1, U10.1, U10.2
PROC_SDIO_CK: R10.1, U1.53, U2.8
PROC_SDIO_D0: R13.1, U1.39, U2.4
PROC_SDIO_D1: R14.1, U1.40, U2.3
PROC_SDIO_D2: R15.1, U1.51, U2.15
PROC_SDIO_D3: R16.1, U1.52, U2.14
PROC_SDIO_D4: R17.1, U1.61, U2.13
PROC_SDIO_D5: R18.1, U1.62, U2.11
PROC_SDIO_D6: R19.1, U1.37, U2.7
PROC_SDIO_D7: R20.1, U1.38, U2.5
PROC_SPI1_MISO: U1.22, U5.14
PROC_SPI1_MOSI: U1.23, U5.11
PROC_SPI1_NSS: U1.20, U5.12
PROC_SPI1_SCK: U1.21, U5.10
VCC_S1_15V4: C22.1, C25.1, C26.1, J1.1, R30.2, U8.4
VCC_TIER1_3V3: C1.1, C2.1, C3.1, C4.1, C5.1, C6.1, C7.1, C14.1, C15.1, C16.1, C17.1, C18.1, C19.1, C20.1, C23.1, C24.1, C27.1, F1.2, R4.2, R5.2, R6.2, R7.2, R8.2, R10.2, R11.2, R12.2, R13.2, R14.2, R15.2, R16.2, R17.2, R18.2, R19.2, R20.2, R22.2, R27.2, R28.2, R29.2, R31.1, R33.2, R34.2, R36.1, U1.1, U1.19, U1.32, U1.48, U1.64, U2.9, U3.8, U4.7, U4.8, U5.6, U5.22, U7.4, U8.5, U9.6, U12.5

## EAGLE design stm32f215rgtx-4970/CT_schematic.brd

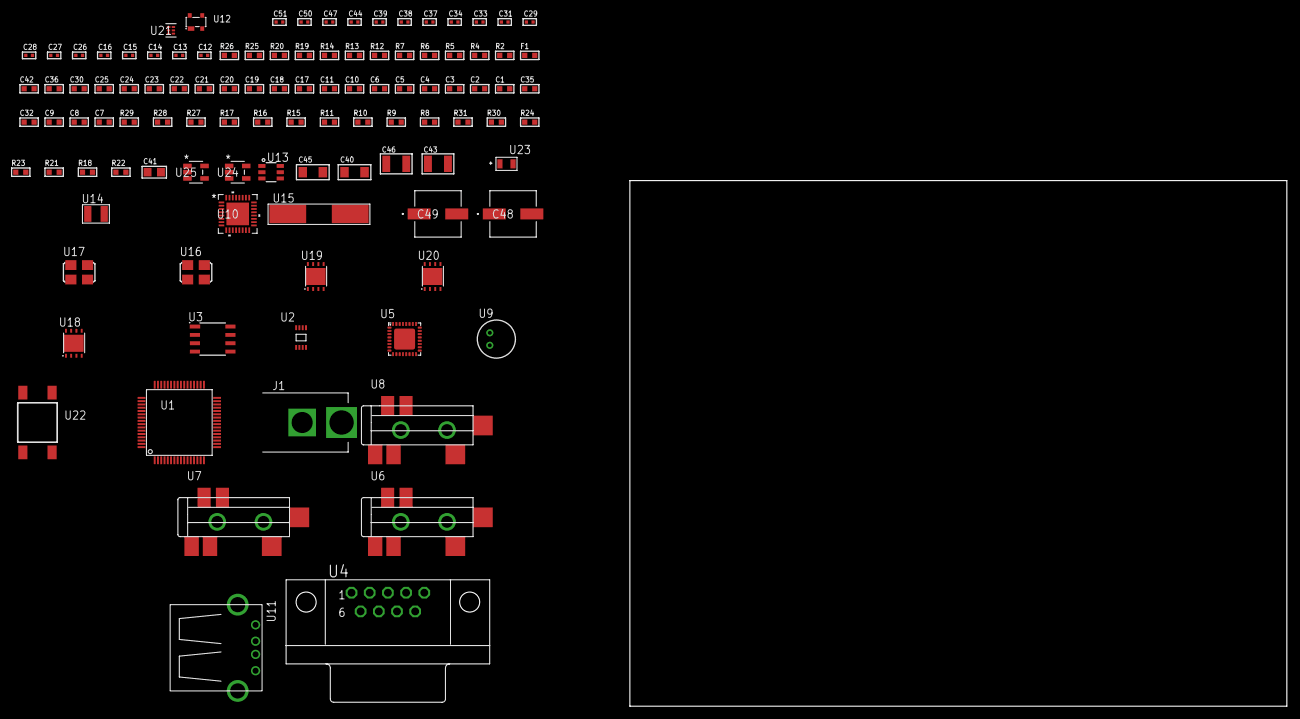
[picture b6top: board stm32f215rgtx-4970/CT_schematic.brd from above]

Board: 2 copper layers, 100.0 x 80.0 mm, 107 parts (0 on the bottom side), 77 nets, no tracks yet.

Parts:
C1, C11, C17, C18, C19, C20, C21, C22, C23, C24, C25, C30, C42: 1e-06; C0603
C2, C3, C4, C5, C6: 1e-07; C0603
C7: 4.7e-06; C0603
C8, C9, C32, C35: 2.2e-06; C0603
C10: 1e-08; C0603
C12, C13, C14, C15: 1e-11; C0402
C16, C37, C38, C39, C44, C50, C51: 1e-08; C0402
C26, C27, C28, C29, C31, C33, C34, C47: 1e-07; C0402
C36: 0.0001; R0603
C40, C45: 1e-05; C1206
C41: 1e-05; C0805
C43, C46: 1e-05; C1210
C48, C49: 0.0001; EXV-9H
F1: 240.0; L0603
J1: PJ-037B; PJ-037B_PACKAGE
R2, R20, R26: 1000.0; R0603
R4, R5: 4700.0; R0603
R6, R7: 2200.0; R0603
R8, R9, R10, R11, R16, R17, R27, R28: 10000.0; R0603
R12: 120.0; R0603
R13, R14: 1270.0; R0603
R15: 47000.0; R0603
R18, R21, R23, R24: 100000.0; R0603
R19: 806.0; R0603
R22: 153694.38; R0603
R25: 3900.0; R0603
R29: 82000.0; R0603
R30: 300000.0; R0603
R31: 120000.0; R0603
U1: STM32F215RGT6; LQFP64
U2: 24AA64T-I/MNY; TDFN-8/6MM
U3: MCP2562-E/SN; SOIC-8
U4: 182-009-113R531; 182-009-MALE
U5: SGTL5000XNAA3; QFN-32
U6, U7, U8: SJ-43515TS-SMT-TR
U9: WM-64PCT; WM-64PC
U10: TUSB1210BRHBR; RHB32_3P45X3P45
U11: 61400416021; USB-A-H
U12: prtr5v0u2ax; SOT143B
U13: MAX4995AAUT+T; SOT-23-6
U14: ABS07-32.768KHZ-7-T
U15: ABLS-25.000MHZ-B2F-T
U16: ASFL1-19.2MHZ-NCS; ASFL1
U17: ASFL-24.57MHZ-NCS; ASFL1
U18, U20: LP3878SDX-ADJ/NOPB; WSON-8
U19: LP2951ACSDX/NOPB; WSON-8
U21: TPS3895ADRYR; SON-6
U22: 4-1437565-2; SW_4-1437565-2
U23: Q65110A2395; LGM67K-G1J2-24-Z
U24, U25: nc7sz125m5x; NC7SZ125M5X

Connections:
CLK_CRYSTAL_U1_3: C12.1, U1.3, U14.1
CLK_CRYSTAL_U1_4: C13.1, U1.4, U14.2
CLK_CRYSTAL_U1_5: C14.1, U1.5, U15.1
CLK_CRYSTAL_U1_6: C15.1, U1.6, U15.2
CLK_U5_21: U5.21, U17.3
CLK_U10_1: U10.1, U16.3
GND: C1.2, C2.2, C3.2, C4.2, C5.2, C6.2, C7.2, C8.2, C9.2, C10.2, C11.2, C12.2, C13.2, C14.2, C15.2, C16.2, C17.2, C18.2, C26.2, C27.2, C28.2, C29.2, C30.2, C31.2, C32.2, C33.2, C34.2, C35.2, C36.2, C37.2, C38.2, C39.2, C40.2, C41.2, C42.2, C43.2, C44.2, C45.2, C46.2, C47.2, C48.2, C49.2, C50.2, C51.2, J1.2, R2.2, R8.2, R9.2, R14.2, R15.2, R17.2, R20.2, R23.2, R26.2, R29.2, R31.2, U1.12, U1.18, U1.63, U2.4, U3.2, U3.8, U4.5, U5.1, U5.3, U5.7, U5.EXP, U7.1, U8.1, U9.2, U10.23, U10.33, U11.4, U11.5, U11.6, U12.1, U13.2, U16.2, U17.2, U18.3, U18.PAD, U19.3, U19.4, U19.PAD, U20.3, U20.PAD, U21.2, U23.C, U24.1, U24.3, U25.1, U25.3
NET_U1_7: R4.1, U1.7, U24.4
NET_U1_13: C10.1, C11.1, F1.1, U1.13
NET_U1_31: C8.1, U1.31
NET_U1_47: C9.1, U1.47
NET_U1_58: R6.1, U1.58, U2.6
NET_U1_59: R7.1, U1.59, U2.5
NET_U1_60: R8.1, U1.60
NET_U1_62: U22.3, U22.4
NET_U2_1: R9.1, U2.1
NET_U2_2: R10.1, U2.2
NET_U2_3: R11.1, U2.3
NET_U3_6: R12.2, U3.6
NET_U4_2: R12.2, U3.6, U4.2
NET_U4_3: R12.1, U3.7, U4.3
NET_U5_10: C29.1, U5.10
NET_U5_29: R13.1, U5.29
NET_U5_31: R14.1, U5.31
NET_U6_1: U5.4, U6.1
NET_U6_2: U5.2, U6.2
NET_U6_5: U5.6, U6.5
NET_U7_2: C20.1, U7.2
NET_U7_5: C19.1, U7.5
NET_U8_2: C22.1, C23.1, U8.2
NET_U8_5: C21.1, U8.5
NET_U8_13: C22.2, C23.2
NET_U9_1: C24.1, C25.1, C30.1, U5.16, U9.1
NET_U9_15: C24.2, C25.2
NET_U10_11: R16.1, U10.11
NET_U10_12: C35.1, U10.12
NET_U10_14: R17.1, U10.14
NET_U10_20: C32.1, U10.20
NET_U10_27: R5.1, U10.27, U25.4
NET_U11_1: C36.1, U10.22, U11.1, U12.4, U13.1
NET_U11_2: U10.19, U11.2, U12.3
NET_U11_3: U10.18, U11.3, U12.2
NET_U13_3: R15.1, U13.3
NET_U13_4: U10.17, U13.4
NET_U18_1: C39.1, U18.1
NET_U18_6: R19.2, R20.1, U18.6
NET_U18_8: R18.1, U18.8
NET_U19_5: R21.1, U19.5
NET_U19_7: R22.2, R23.1, U19.7
NET_U20_1: C44.1, U20.1
NET_U20_6: R25.2, R26.1, U20.6
NET_U20_8: R24.1, U20.8
NET_U21_1: R28.1, R29.1, U21.1
NET_U21_3: R30.2, R31.1, U21.3
NET_U21_4: R27.1, U21.4, U24.2, U25.2
NET_U22_1: R2.1, U22.1, U22.2
PROC_CAN1_RX: U1.44, U3.4
PROC_CAN1_TX: U1.45, U3.1
PROC_I2S3_SCK: U1.51, U5.24
PROC_I2S3_SD: U1.53, U5.26
PROC_I2S3_WS: U1.20, U5.23
PROC_USB_OTG_HS_ULPI_CK: U1.21, U10.26
PROC_USB_OTG_HS_ULPI_D0: U1.17, U10.3
PROC_USB_OTG_HS_ULPI_D1: U1.26, U10.4
PROC_USB_OTG_HS_ULPI_D2: U1.27, U10.5
PROC_USB_OTG_HS_ULPI_D3: U1.29, U10.6
PROC_USB_OTG_HS_ULPI_D4: U1.30, U10.7
PROC_USB_OTG_HS_ULPI_D5: U1.33, U10.9
PROC_USB_OTG_HS_ULPI_D6: U1.34, U10.10
PROC_USB_OTG_HS_ULPI_D7: U1.57, U10.13
PROC_USB_OTG_HS_ULPI_DIR: U1.10, U10.31
PROC_USB_OTG_HS_ULPI_NXT: U1.11, U10.2
PROC_USB_OTG_HS_ULPI_STP: U1.8, U10.29
VCC_S1_8V1: C40.1, C42.1, C45.1, C48.1, C49.1, J1.1, R18.2, R24.2, U18.4, U19.8, U20.4
VCC_TIER1_1V8: C1.1, C2.1, C3.1, C4.1, C5.1, C6.1, C7.1, C16.1, C18.1, C26.1, C27.1, C28.1, C33.1, C34.1, C41.1, C47.1, C50.1, C51.1, F1.2, R4.2, R5.2, R6.2, R7.2, R10.2, R11.2, R13.2, R16.2, R19.1, R27.2, R28.2, R30.1, U1.1, U1.19, U1.32, U1.48, U1.64, U2.7, U2.8, U3.5, U5.5, U5.20, U5.30, U10.28, U10.30, U10.32, U18.5, U21.6, U24.5, U25.5
VCC_TIER1_3V3: C31.1, C37.1, C38.1, C43.1, R21.2, R22.1, U10.21, U16.4, U17.4, U19.1
VCC_TIER1_5V0: C17.1, C46.1, R25.1, U3.3, U13.5, U20.5
